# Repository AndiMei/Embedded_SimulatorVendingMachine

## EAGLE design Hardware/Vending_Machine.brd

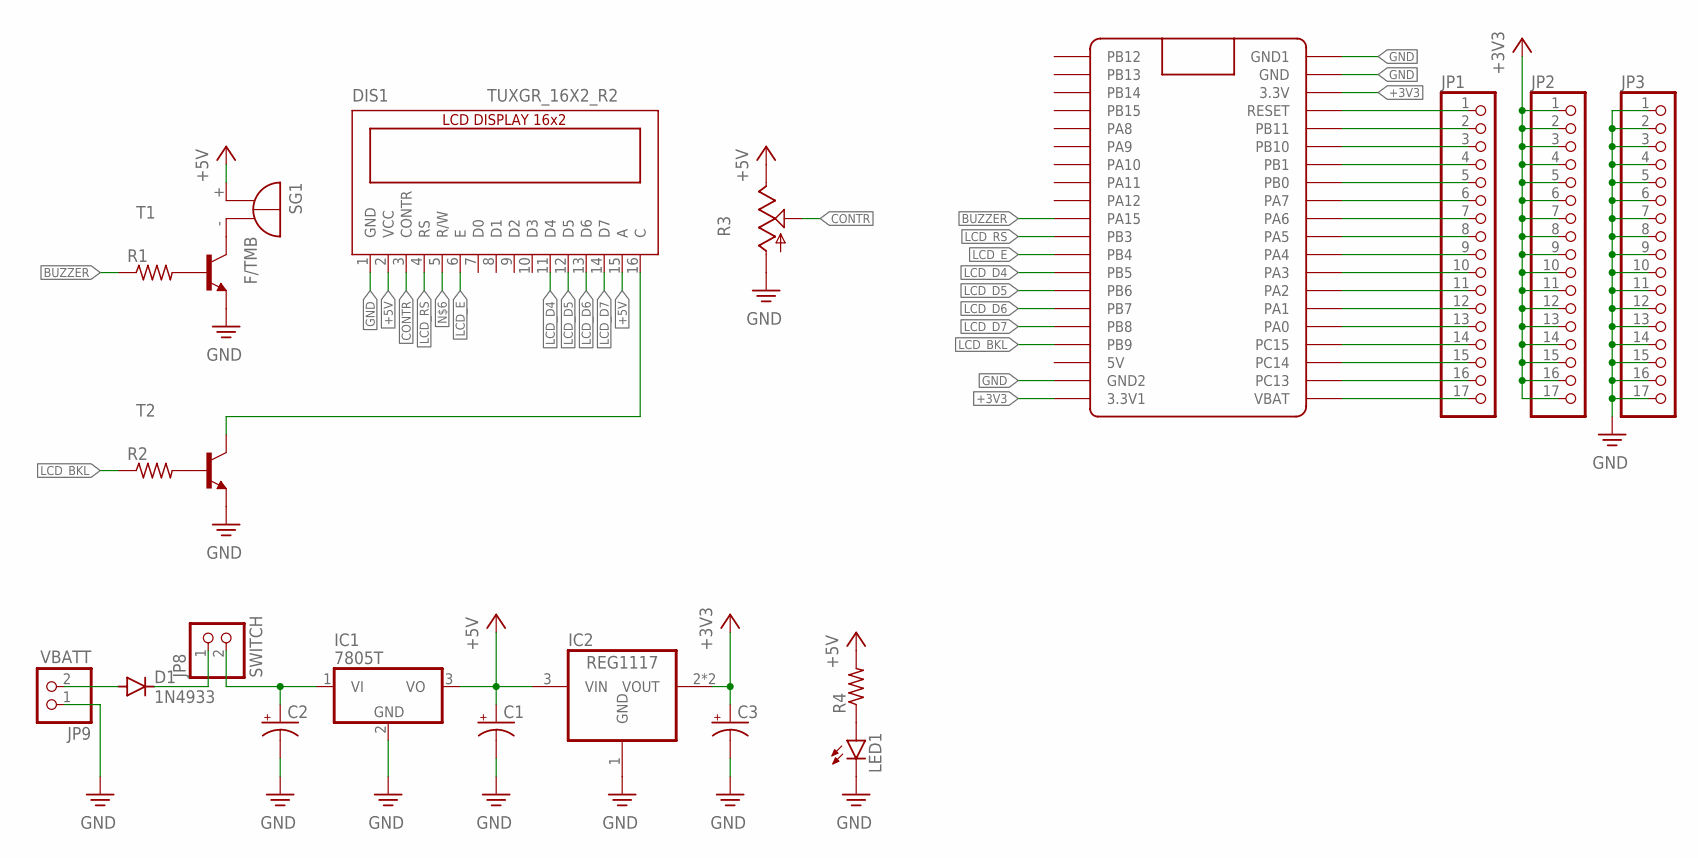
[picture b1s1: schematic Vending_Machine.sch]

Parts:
C1, C2, C3: CPOL-USE2.5-6; E2,5-6
D1: 1N4933; DO41-10
DIS1: TUXGR_16X2_R2
IC1: 7805T; TO220H
IC2: REG1117; SOT223
JP1, JP2, JP3: PINHD-1X17; 1X17
JP8: SWITCH; 1X02
JP9: VBATT; 1X02
LED1: LED3MM
R1, R2, R4: R-US_0204/7; 0204/7
R3: TRIM_US-CA6V; CA6V
SG1: F/TMB
T1, T2: BC167-NPN-TO92-ECB; TO92-ECB
U$1: BLUE_PILL

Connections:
+3V3: C3.+, IC2.2 (VOUT), IC2.4 (VOUT), JP2.1, JP2.2, JP2.3, JP2.4, JP2.5, JP2.6, JP2.7, JP2.8, JP2.9, JP2.10, JP2.11, JP2.12, JP2.13, JP2.14, JP2.15, JP2.16, JP2.17, U$1.P$20 (3.3V1), U$1.P$23 (3.3V)
+5V: C1.+, DIS1.2 (VCC), DIS1.15 (A), IC1.3 (VO), IC2.3 (VIN), R3.E, R4.2, SG1.+
BUZZER: R1.1, U$1.P$10 (PA15)
CONTR: DIS1.3 (CONTR), R3.S
GND: C1.-, C2.-, C3.-, DIS1.1 (GND), IC1.2 (GND), IC2.1 (GND), JP3.1, JP3.2, JP3.3, JP3.4, JP3.5, JP3.6, JP3.7, JP3.8, JP3.9, JP3.10, JP3.11, JP3.12, JP3.13, JP3.14, JP3.15, JP3.16, JP3.17, JP9.1, LED1.K (C), R3.A, T1.E, T2.E, U$1.P$19 (GND2), U$1.P$21 (GND1), U$1.P$22 (GND)
LCD_BKL: R2.1, U$1.P$17 (PB9)
LCD_D4: DIS1.11 (D4), U$1.P$13 (PB5)
LCD_D5: DIS1.12 (D5), U$1.P$14 (PB6)
LCD_D6: DIS1.13 (D6), U$1.P$15 (PB7)
LCD_D7: DIS1.14 (D7), U$1.P$16 (PB8)
LCD_E: DIS1.6 (E), U$1.P$12 (PB4)
LCD_RS: DIS1.4 (RS), U$1.P$11 (PB3)
unnamed: SG1.-, T1.C
unnamed: R1.2, T1.B
unnamed: R2.2, T2.B
unnamed: JP1.17, U$1.P$40 (VBAT)
unnamed: C2.+, IC1.1 (VI), JP8.2
unnamed: D1.C, JP8.1
unnamed: D1.A, JP9.2
unnamed: LED1.A, R4.1
unnamed: DIS1.16 (C), T2.C
PA0: JP1.13, U$1.P$36 (PA0)
PA1: JP1.12, U$1.P$35 (PA1)
PA2: JP1.11, U$1.P$34 (PA2)
PA3: JP1.10, U$1.P$33 (PA3)
PA4: JP1.9, U$1.P$32 (PA4)
PA5: JP1.8, U$1.P$31 (PA5)
PA6: JP1.7, U$1.P$30 (PA6)
PB1: JP1.4, U$1.P$27 (PB1)
PB10: JP1.3, U$1.P$26 (PB10)
PB11: JP1.2, U$1.P$25 (PB11)
PB_BATAL: JP1.6, U$1.P$29 (PA7)
PB_START: JP1.5, U$1.P$28 (PB0)
PC13: JP1.16, U$1.P$39 (PC13)
PC14: JP1.15, U$1.P$38 (PC14)
PC15: JP1.14, U$1.P$37 (PC15)
RESET: JP1.1, U$1.P$24 (RESET)

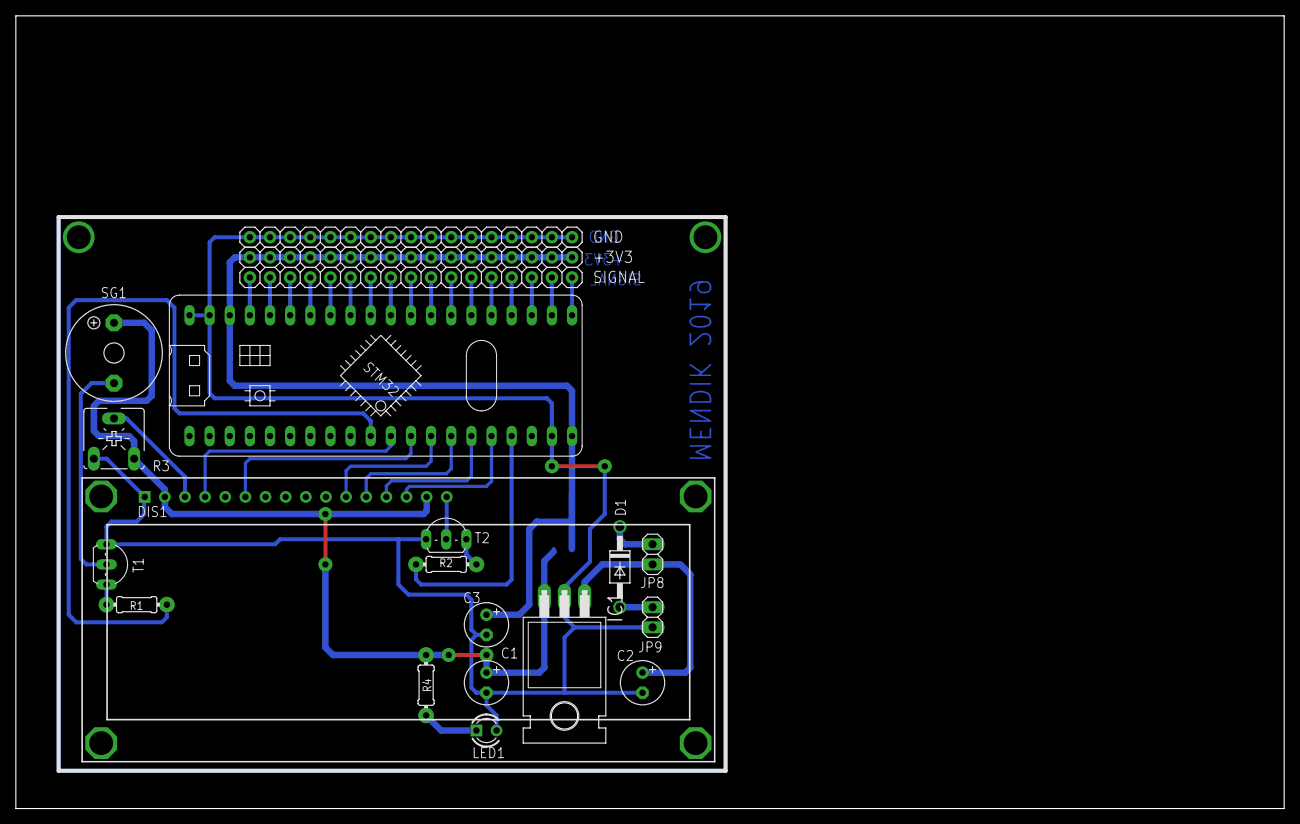
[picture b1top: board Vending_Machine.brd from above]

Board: 2 copper layers, 160.0 x 100.0 mm, 21 parts (1 on the bottom side), 37 nets.

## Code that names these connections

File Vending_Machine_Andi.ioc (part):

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Mcu.Name=STM32F103C(8-B)Tx
Mcu.Package=LQFP48
Mcu.UserName=STM32F103C8Tx
PA0-WKUP.Signal=ADCx_IN0
PA13.Mode=Serial_Wire
PA13.Signal=SYS_JTMS-SWDIO
PA14.Mode=Serial_Wire
PA14.Signal=SYS_JTCK-SWCLK
PA15.GPIOParameters=GPIO_Label
PA15.GPIO_Label=BUZZER
PA15.Signal=GPIO_Output
PA4.GPIOParameters=GPIO_PuPd,GPIO_Label
PA4.GPIO_Label=PB_PROCESS
PA4.GPIO_PuPd=GPIO_PULLUP
PA4.Signal=GPIO_Input
PA5.GPIOParameters=GPIO_PuPd,GPIO_Label
PA5.GPIO_Label=PB_CANCEL
PA5.GPIO_PuPd=GPIO_PULLUP
PA5.Signal=GPIO_Input
PB0.GPIOParameters=GPIO_Label
PB0.GPIO_Label=LED_BLUE
PB0.Signal=GPIO_Output
PB1.GPIOParameters=GPIO_Label
PB1.GPIO_Label=LED_RED
PB1.Signal=GPIO_Output
PB10.GPIOParameters=GPIO_Label
PB10.GPIO_Label=LED_YELLOW
PB10.Signal=GPIO_Output
PB11.GPIOParameters=GPIO_Label
PB11.GPIO_Label=LED_GREEN
PB11.Signal=GPIO_Output
PB3.GPIOParameters=GPIO_Label
PB3.GPIO_Label=LCD_RS
PB3.Signal=GPIO_Output
PB4.GPIOParameters=GPIO_Label
PB4.GPIO_Label=LCD_E
PB4.Signal=GPIO_Output
PB5.GPIOParameters=GPIO_Label
PB5.GPIO_Label=LCD_D4
PB5.Signal=GPIO_Output
PB6.GPIOParameters=GPIO_Label
PB6.GPIO_Label=LCD_D5
PB6.Signal=GPIO_Output
PB7.GPIOParameters=GPIO_Label
PB7.GPIO_Label=LCD_D6
PB7.Signal=GPIO_Output
PB8.GPIOParameters=GPIO_Label
PB8.GPIO_Label=LCD_D7
PB8.Signal=GPIO_Output
PB9.GPIOParameters=GPIO_Label
PB9.GPIO_Label=LCD_BKL
PB9.Signal=GPIO_Output
PD0-OSC_IN.Mode=HSE-External-Oscillator
PD0-OSC_IN.Signal=RCC_OSC_IN
PD1-OSC_OUT.Mode=HSE-External-Oscillator
PD1-OSC_OUT.Signal=RCC_OSC_OUT
RCC.SYSCLKFreq_VALUE=72000000
RCC.SYSCLKSource=RCC_SYSCLKSOURCE_PLLCLK
board=custom

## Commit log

2019-12-01 Program Final
